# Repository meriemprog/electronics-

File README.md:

https://github.com/user-attachments/assets/29fd35da-6b59-4d50-ba5c-595f73e152a5

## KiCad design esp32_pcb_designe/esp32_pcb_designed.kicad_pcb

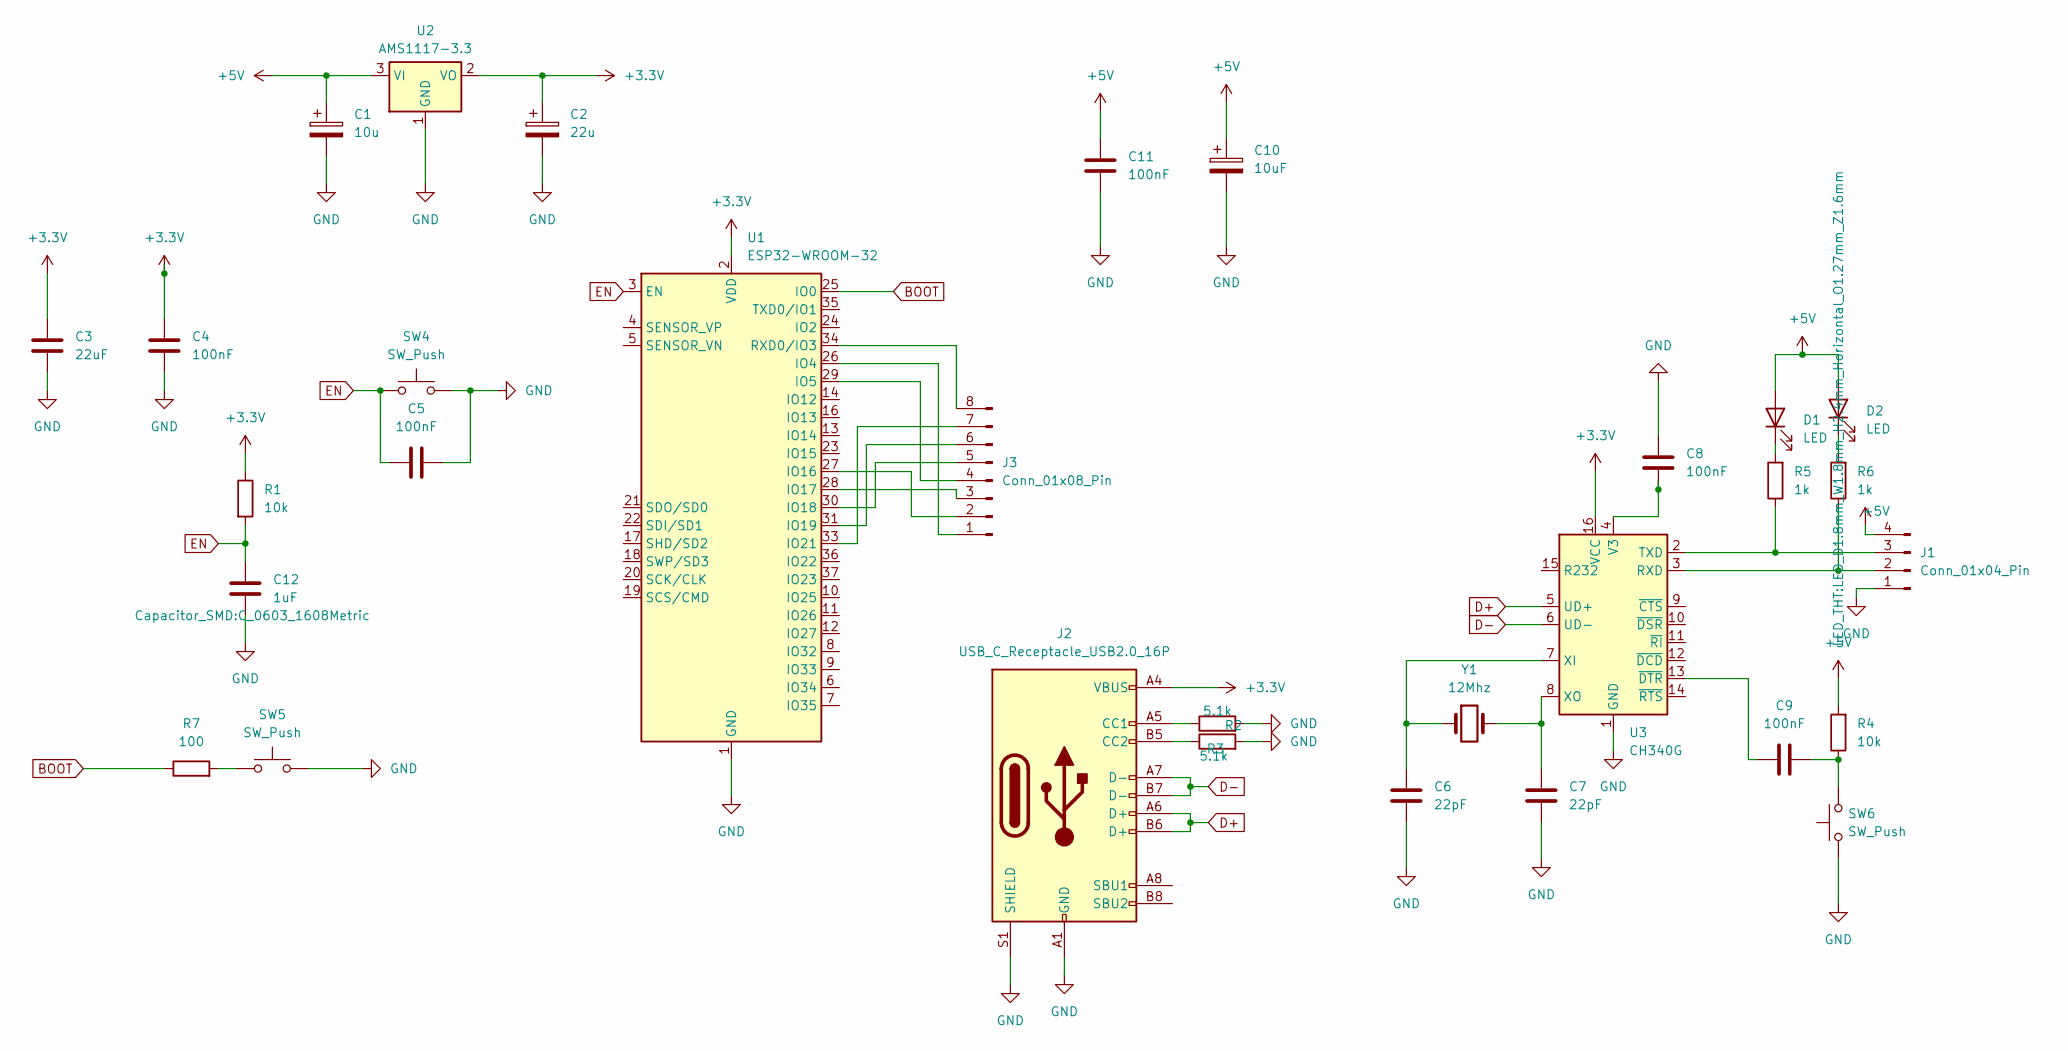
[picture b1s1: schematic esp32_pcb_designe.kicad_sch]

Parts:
C1: 10u; CP_EIA-3216-18_Kemet-A
C2: 22u; CP_EIA-3528-21_Kemet-B
C3: 22uF; C_1206_3216Metric
C4, C5, C9, C11: 100nF; C_0805_2012Metric
C6, C7: 22pF; C_0603_1608Metric
C8: 100nF; CP_Axial_L10.0mm_D4.5mm_P15.00mm_Horizontal
C10: 10uF; CP_EIA-3216-18_Kemet-A
C12: 1uF; C_0603_1608Metric
D1, D2: LED; LED_D1.8mm_W1.8mm_H2.4mm_Horizontal_O1.27mm_Z1.6mm
J1: Conn_01x04_Pin; PinHeader_1x04_P1.00mm_Horizontal
J2: USB_C_Receptacle_USB2.0_16P; USB_C_Receptacle_HCTL_HC-TYPE-C-16P-01A
J3: Conn_01x08_Pin; PinHeader_1x08_P1.00mm_Horizontal
R1, R4: 10k; R_0805_2012Metric
R2, R3: 5.1k; R_0805_2012Metric
R5, R6: 1k; R_0805_2012Metric
R7: 100; R_0805_2012Metric
SW4, SW5, SW6: SW_Push; SW_DIP_SPSTx01_Slide_6.7x4.1mm_W7.62mm_P2.54mm_LowProfile
U1: ESP32-WROOM-32
U2: AMS1117-3.3; SOT-223-3_TabPin2
U3: CH340G; SOIC-16_3.9x9.9mm_P1.27mm
Y1: 12Mhz; Crystal_HC18-U_Horizontal

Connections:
+3.3V: C2.1, C3.1, C4.1, J2.A4 (VBUS), J2.A9 (VBUS), J2.B4 (VBUS), J2.B9 (VBUS), R1.1, U1.2 (VDD), U2.2 (VO), U3.16 (VCC)
+5V: C1.1, C10.1, C11.2, D1.2 (A), D2.2 (A), J1.4, R4.2, U2.3 (VI)
BOOT: R7.1, U1.25 (IO0)
D+: J2.A6 (D+), J2.B6 (D+), U3.5 (UD+)
D-: J2.A7 (D-), J2.B7 (D-), U3.6 (UD-)
EN: C5.1, C12.1, R1.2, SW4.1, U1.3 (EN)
GND: C1.2, C2.2, C3.2, C4.2, C5.2, C6.1, C7.1, C8.2, C10.2, C11.1, C12.2, J1.1, J2.A1 (GND), J2.A12 (GND), J2.B1 (GND), J2.B12 (GND), J2.S1 (SHIELD), R2.2, R3.2, SW4.2, SW5.2, SW6.1, U1.1 (GND), U1.15 (GND), U1.38 (GND), U1.39 (GND), U2.1 (GND), U3.1 (GND)
unnamed: C9.1, R4.1, SW6.2
unnamed: D1.1 (K), R5.2
unnamed: D2.1 (K), R6.2
unnamed: J1.2, R6.1, U3.3 (RXD)
unnamed: J1.3, R5.1, U3.2 (TXD)
unnamed: J2.A5 (CC1), R2.1
unnamed: J2.B5 (CC2), R3.1
unnamed: J3.1, U1.26 (IO4)
unnamed: J3.2, U1.27 (IO16)
unnamed: J3.3, U1.28 (IO17)
unnamed: J3.4, U1.29 (IO5)
unnamed: J3.5, U1.30 (IO18)
unnamed: J3.6, U1.31 (IO19)
unnamed: J3.7, U1.33 (IO21)
unnamed: J3.8, U1.34 (RXD0/IO3)
unnamed: R7.2, SW5.1
unnamed: C8.1, U3.4 (V3)
unnamed: C6.2, U3.7 (XI), Y1.1
unnamed: C7.2, U3.8 (XO), Y1.2
unnamed: C9.2, U3.13 (~DTR)

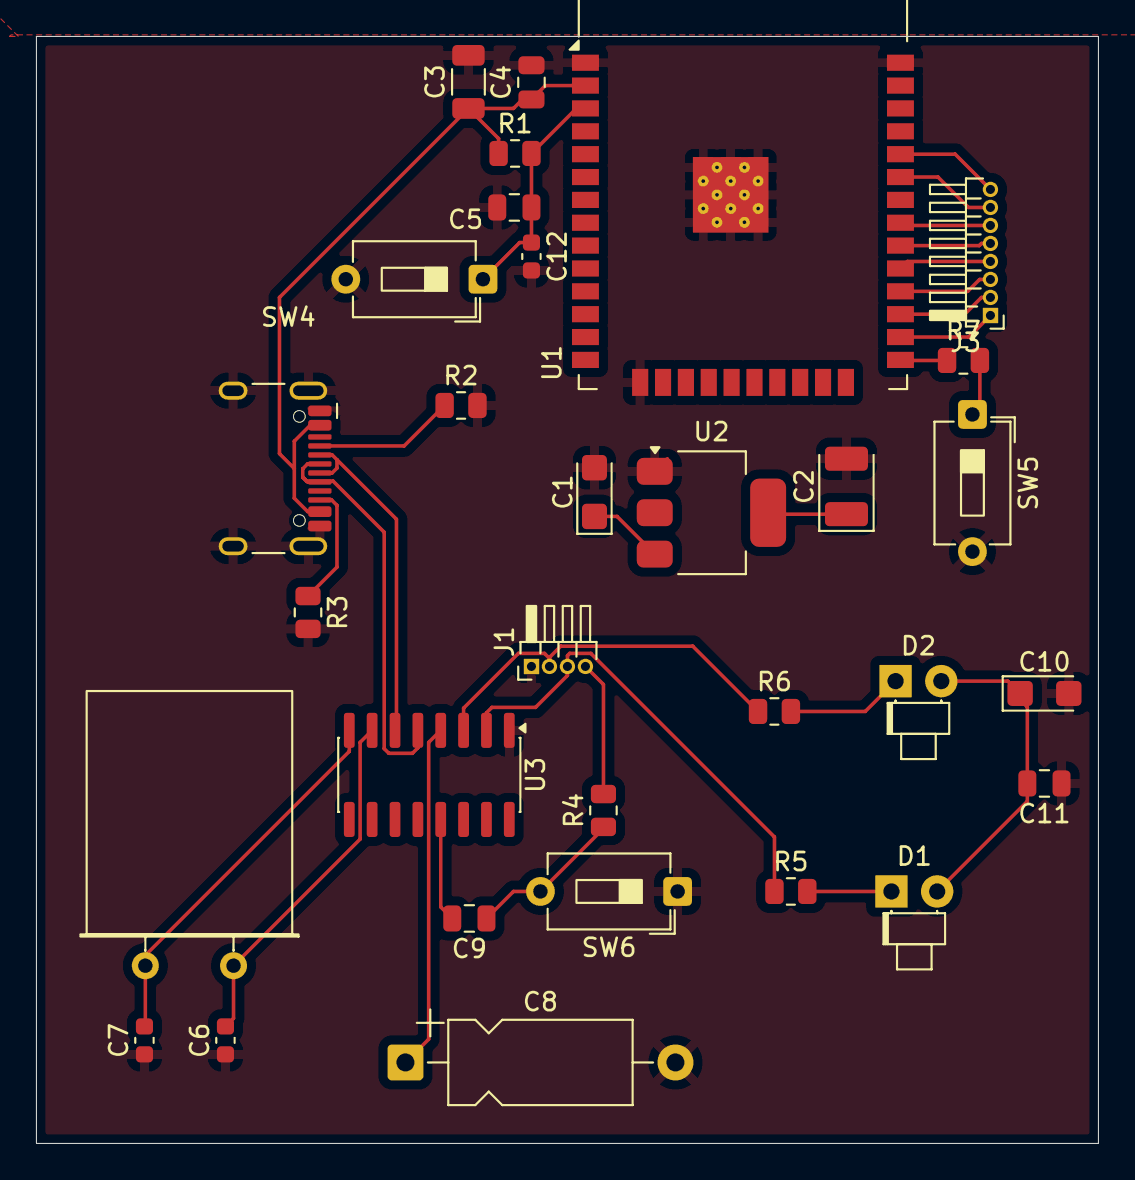
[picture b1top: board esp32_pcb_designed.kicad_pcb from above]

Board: 2 copper layers, 59.0 x 61.5 mm, 31 parts (0 on the bottom side), 27 nets.
